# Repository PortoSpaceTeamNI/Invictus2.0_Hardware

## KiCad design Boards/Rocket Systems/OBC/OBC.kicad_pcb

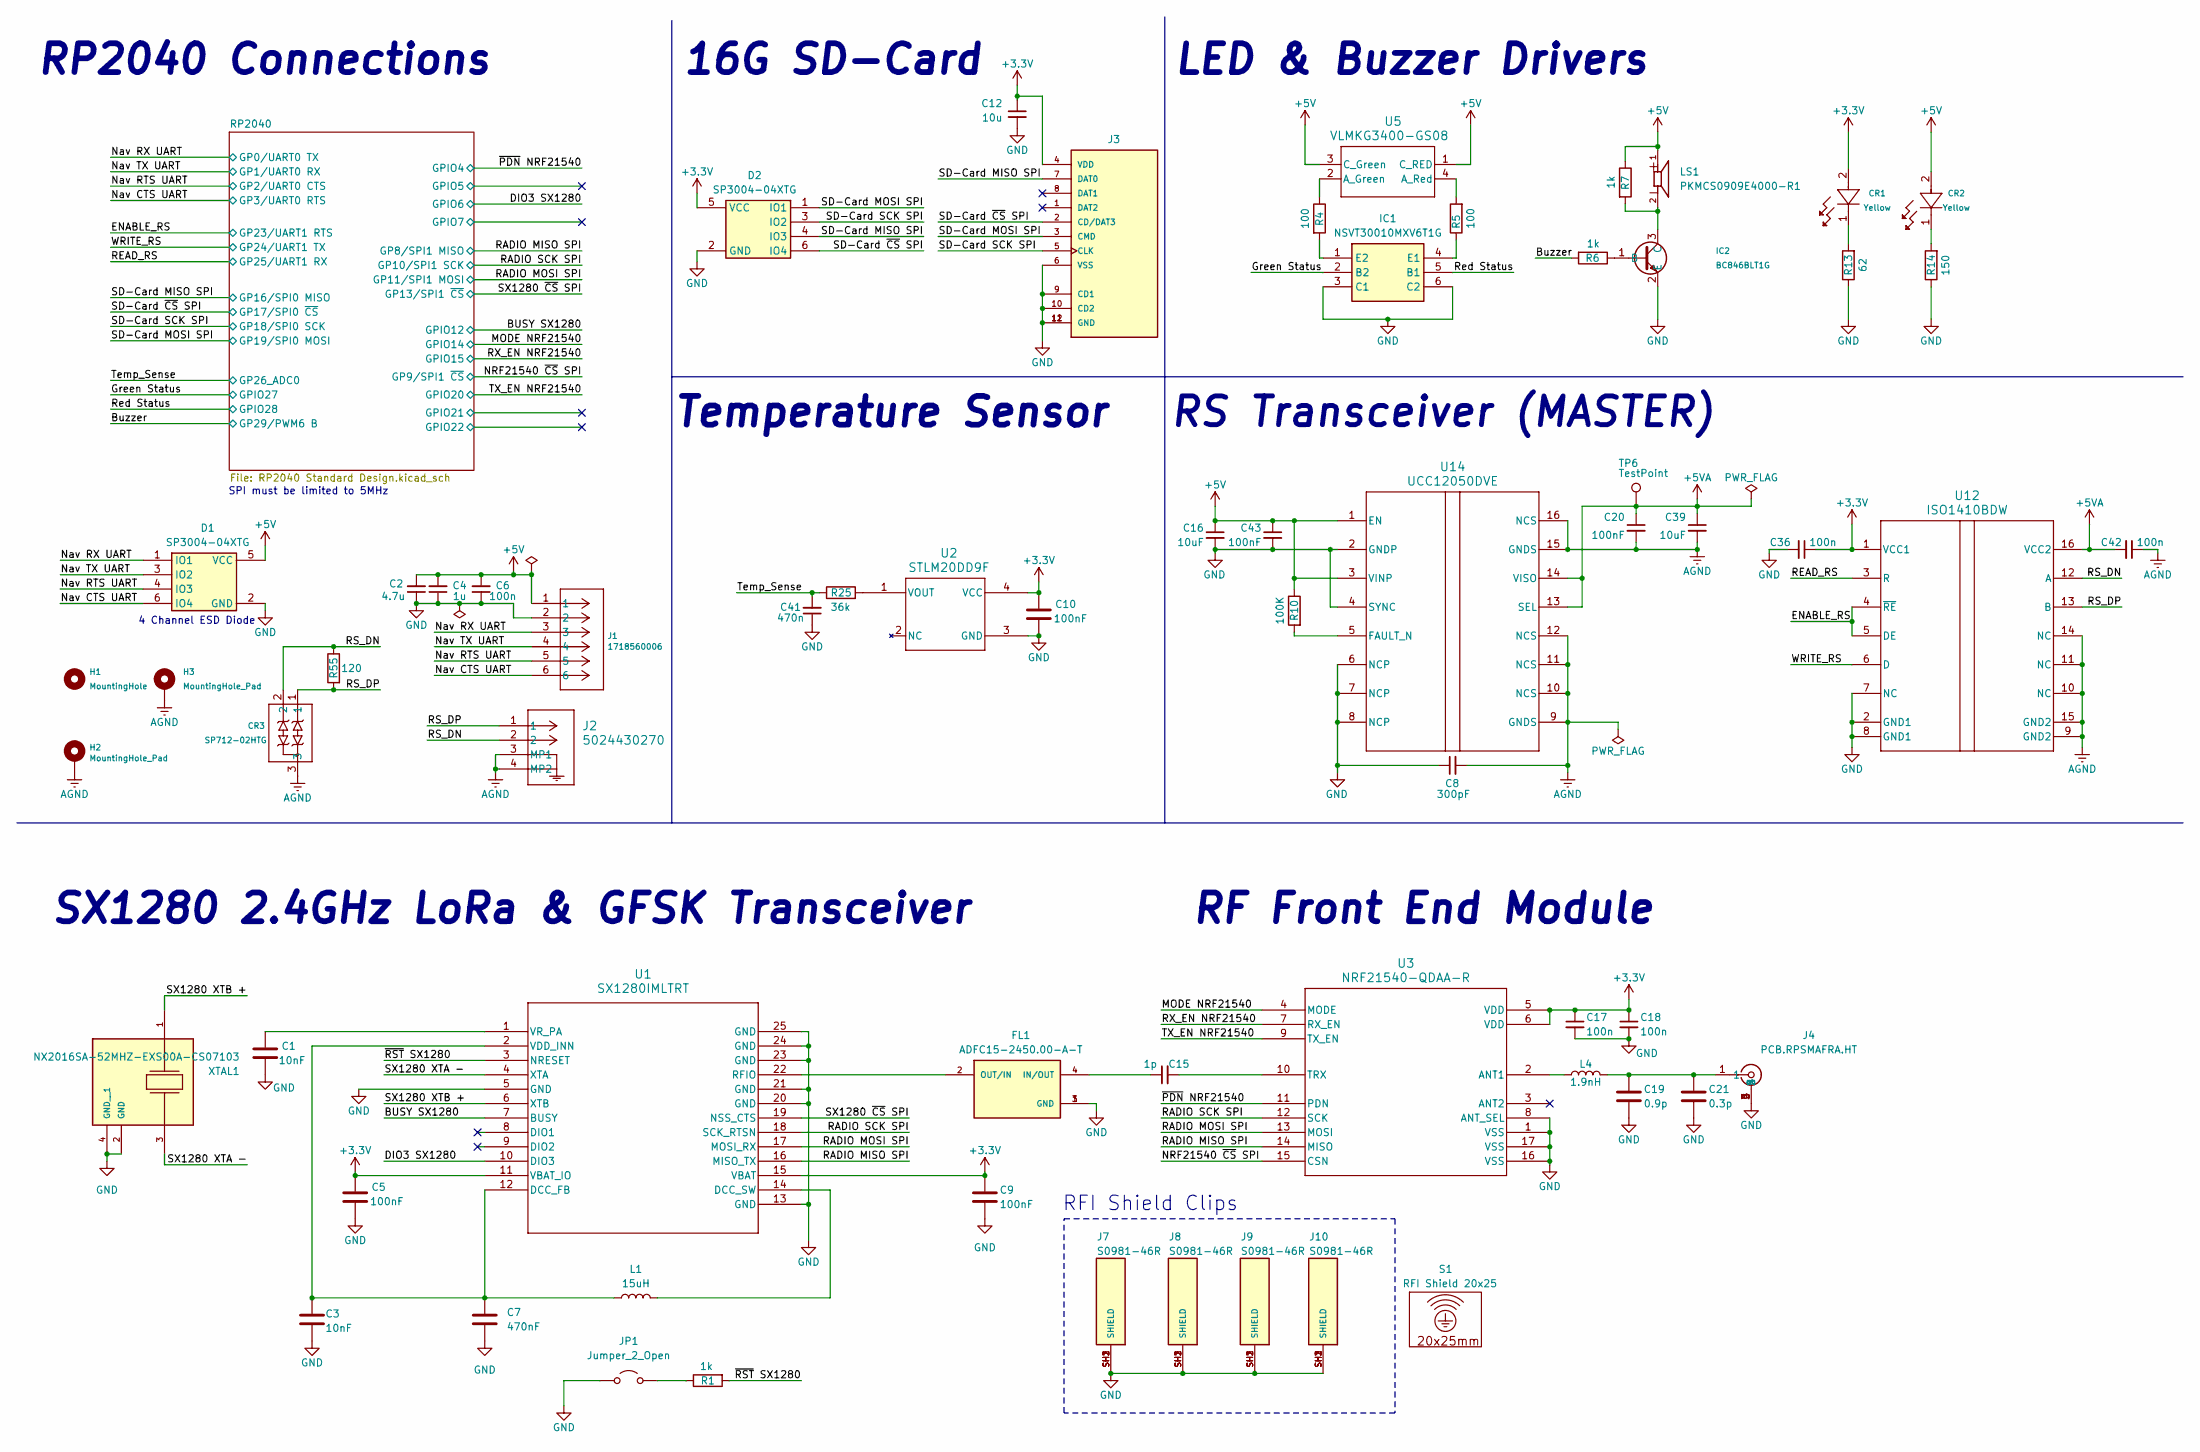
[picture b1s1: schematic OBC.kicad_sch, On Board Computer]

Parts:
C1, C3: 10nF; Capacitor_0402
C2: 4.7u; Capacitor_0603
C4: 1u; Capacitor_0402
C5, C9, C10, C20, C43: 100nF; Capacitor_0402
C6, C17, C18, C36, C42: 100n; Capacitor_0402
C7: 470nF; Capacitor_0402
C8: 300pF; C1808
C12: 10u; Capacitor_0805
C15: 1p; Capacitor_0402
C16, C39: 10uF; Capacitor_0805
C19: 0.9p; Capacitor_0402
C21: 0.3p; Capacitor_0402
C41: 470n; Capacitor_0402
CR1, CR2: VLMY1300-GS08; LEDC1608X100N
CR3: SP712-02HTG; SOT23-3_LTF
D1, D2: SP3004-04XTG; SOT563_LTF; Mouser Part Number 576-SP3004-04XTG
FL1: ADFC15-2450.00-A-T; FIL_ADFC15-2450.00-A-T; PARTREV 12.03.12
H1: MountingHole; MountingHole_3.2mm_M3_ISO7380
H2, H3: MountingHole_Pad; MountingHole_3.2mm_M3_ISO7380_Pad
IC1: NSVT30010MXV6T1G; SOTFL50P160X60-6N; Mouser Part Number 863-NSVT30010MXV6T1G
IC2: BC846BLT1G; SOT-23_ONS; Mouser Part Number 863-BC846BLT1G
J1: 1718560006; CONN06_1718560006_MOL
J2: 5024430270; CONN_502443-02xx_MOL
J3: MEM2061-01-188-00-A_REVA; GCT_MEM2061-01-188-00-A_REVA
J4: PCB.RPSMAFRA.HT; PCBRPSMAFRAHT; Mouser Part Number 960-PCB.RPSMAFRA.HT
J7, J8, J9, J10: S0981-46R; HARWIN_S0981-46R; PARTREV 3
JP1: Jumper_2_Open; SolderJumper-2_P1.3mm_Open_RoundedPad1.0x1.5mm
L1: 15uH; Inductor_0805
L4: 1.9nH; Inductor_0201
LS1: PKMCS0909E4000-R1; SPKR_PKMCS0909E4000-R1; PARTREV May 22, 2020
R1: 1k; RES_0402
R4, R5: 100; RES_0603
R6, R7: 1k; RES_0603
R10: 100K; RES_0402
R13: 62; RES_0603
R14: 150; RES_0603
R25: 36k; RES_0402
R55: 120; RES_0603
S1: RFI Shield 20x25; RFI Shield
TP6: TestPoint; TestPoint_Pad_2.0x2.0mm
U1: SX1280IMLTRT; QFN24_4X4_SEM
U2: STLM20DD9F; UDFN-4L_STM
U3: NRF21540-QDAA-R; QFN16_4X4_NOR
U5: VLMKG3400-GS08; SMT_00-GS08_VIS
U12: ISO1410BDW; DW0016B_N
U14: UCC12050DVE; DVE0016A
XTAL1: NX2016SA-52MHZ-EXS00A-CS07103; OSCCC200X160X50N; PARTREV N/A

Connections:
+3.3V: C5.1, C9.1, C10.1, C12.1, C17.1, C18.1, C36.1, CR1.2, D2.5 (VCC), J3.4 (VDD), U1.11 (VBAT_IO), U1.15 (VBAT), U2.4 (VCC), U3.5 (VDD), U3.6 (VDD), U12.1 (VCC1); also elsewhere on the board
+5V: C2.2, C4.2, C6.2, C16.1, C43.1, CR2.2, D1.5 (VCC), J1.1, LS1.1, R7.1, R10.1, U5.1 (C_RED), U5.3 (C_Green), U14.1 (EN), U14.3 (VINP); also elsewhere on the board
+5VA: C20.1, C39.1, C42.2, TP6.1, U12.16 (VCC2), U14.13 (SEL), U14.14 (VISO)
/BUSY SX1280: U1.7 (BUSY); also elsewhere on the board
/Buzzer: R6.2; also elsewhere on the board
/DIO3 SX1280: U1.10 (DIO3); also elsewhere on the board
/ENABLE_RS: U12.4 (~RE), U12.5 (DE); also elsewhere on the board
/Green Status: IC1.2 (B2); also elsewhere on the board
/MODE NRF21540: U3.4 (MODE); also elsewhere on the board
/NRF21540 ~CS SPI: U3.15 (CSN); also elsewhere on the board
/Nav CTS UART: D1.6 (IO4), J1.6; also elsewhere on the board
/Nav RTS UART: D1.4 (IO3), J1.5; also elsewhere on the board
/Nav RX UART: D1.1 (IO1), J1.3; also elsewhere on the board
/Nav TX UART: D1.3 (IO2), J1.4; also elsewhere on the board
/RADIO MISO SPI: U1.16 (MISO_TX), U3.14 (MISO); also elsewhere on the board
/RADIO MOSI SPI: U1.17 (MOSI_RX), U3.13 (MOSI); also elsewhere on the board
/RADIO SCK SPI: U1.18 (SCK_RTSN), U3.12 (SCK); also elsewhere on the board
/READ_RS: U12.3 (R); also elsewhere on the board
/RS_DN: CR3.2, J2.2, R55.1, U12.12 (A)
/RS_DP: CR3.1, J2.1, R55.2, U12.13 (B)
/RX_EN NRF21540: U3.7 (RX_EN); also elsewhere on the board
/Red Status: IC1.5 (B1); also elsewhere on the board
/SD-Card ~CS SPI: D2.6 (IO4), J3.2 (CD/DAT3); also elsewhere on the board
/SD-Card MISO SPI: D2.4 (IO3), J3.7 (DAT0); also elsewhere on the board
/SD-Card MOSI SPI: D2.1 (IO1), J3.3 (CMD); also elsewhere on the board
/SD-Card SCK SPI: D2.3 (IO2), J3.5 (CLK); also elsewhere on the board
/SX1280 XTA -: U1.4 (XTA), XTAL1.3
/SX1280 XTB +: U1.6 (XTB), XTAL1.1
/SX1280 ~CS SPI: U1.19 (NSS_CTS); also elsewhere on the board
/TX_EN NRF21540: U3.9 (TX_EN); also elsewhere on the board
/Temp_Sense: C41.2, R25.1; also elsewhere on the board
/WRITE_RS: U12.6 (D); also elsewhere on the board
/~PDN NRF21540: U3.11 (PDN); also elsewhere on the board
/~RST SX1280: R1.2, U1.3 (NRESET)
AGND: C8.2, C20.2, C39.2, C42.1, CR3.3, H2.1, H3.1, J2.3 (MP1), J2.4 (MP2), U12.9 (GND2), U12.10 (NC), U12.11 (NC), U12.14 (NC), U12.15 (GND2), U14.9 (GNDS), U14.10 (NCS), U14.11 (NCS), U14.12 (NCS), U14.15 (GNDS), U14.16 (NCS)
GND: C1.2, C2.1, C3.2, C4.1, C5.2, C6.1, C7.2, C8.1, C9.2, C10.2, C12.2, C16.2, C17.2, C18.2, C19.2, C21.2, C36.2, C41.1, C43.2, D1.2 (GND), D2.2 (GND), FL1.1 (GND), FL1.3 (GND), IC1.3 (C1), IC1.6 (C2), IC2.2 (E), J1.2, J3.6 (VSS), J3.9 (CD1), J3.10 (CD2), J3.11 (GND), J3.12 (GND), J4.2, J4.3, J4.4, J4.5, J7.SH1 (SHIELD), J7.SH2 (SHIELD), J7.SH3 (SHIELD), J8.SH1 (SHIELD), J8.SH2 (SHIELD), J8.SH3 (SHIELD), J9.SH1 (SHIELD), J9.SH2 (SHIELD), J9.SH3 (SHIELD), J10.SH1 (SHIELD), J10.SH2 (SHIELD), J10.SH3 (SHIELD), JP1.1 (A), R13.1, R14.1, U1.5 (GND), U1.13 (GND), U1.20 (GND), U1.21 (GND), U1.23 (GND), U1.24 (GND), U1.25 (GND), U2.3 (GND), U3.1 (VSS), U3.8 (ANT_SEL), U3.16 (VSS), U3.17 (VSS), U12.2 (GND1), U12.7 (NC), U12.8 (GND1), U14.2 (GNDP), U14.4 (SYNC), U14.6 (NCP), U14.7 (NCP), U14.8 (NCP), XTAL1.2 (GND), XTAL1.4 (GND__1); also elsewhere on the board
unnamed: C19.1, C21.1, J4.1, L4.2
unnamed: CR1.1, R13.2
unnamed: CR2.1, R14.2
unnamed: C15.1, FL1.4 (IN/OUT)
unnamed: FL1.2 (OUT/IN), U1.22 (RFIO)
unnamed: IC1.4 (E1), R5.1
unnamed: IC1.1 (E2), R4.2
unnamed: IC2.1 (B), R6.1
unnamed: IC2.3 (C), LS1.2, R7.2
unnamed: JP1.2 (B), R1.1
unnamed: C3.1, C7.1, L1.1, U1.2 (VDD_INN), U1.12 (DCC_FB)
unnamed: L1.2, U1.14 (DCC_SW)
unnamed: C1.1, U1.1 (VR_PA)
unnamed: R25.2, U2.1 (VOUT)
unnamed: L4.1, U3.2 (ANT1)
unnamed: C15.2, U3.10 (TRX)
unnamed: R4.1, U5.2 (A_Green)
unnamed: R5.2, U5.4 (A_Red)
unnamed: R10.2, U14.5 (FAULT_N)

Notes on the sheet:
RF Front End Module
Temperature Sensor
SX1280 2.4GHz LoRa & GFSK Transceiver
RP2040 Connections
SPI must be limited to 5MHz
16G SD-Card
RS Transceiver (MASTER)
LED & Buzzer Drivers
RFI Shield Clips
4 Channel ESD Diode

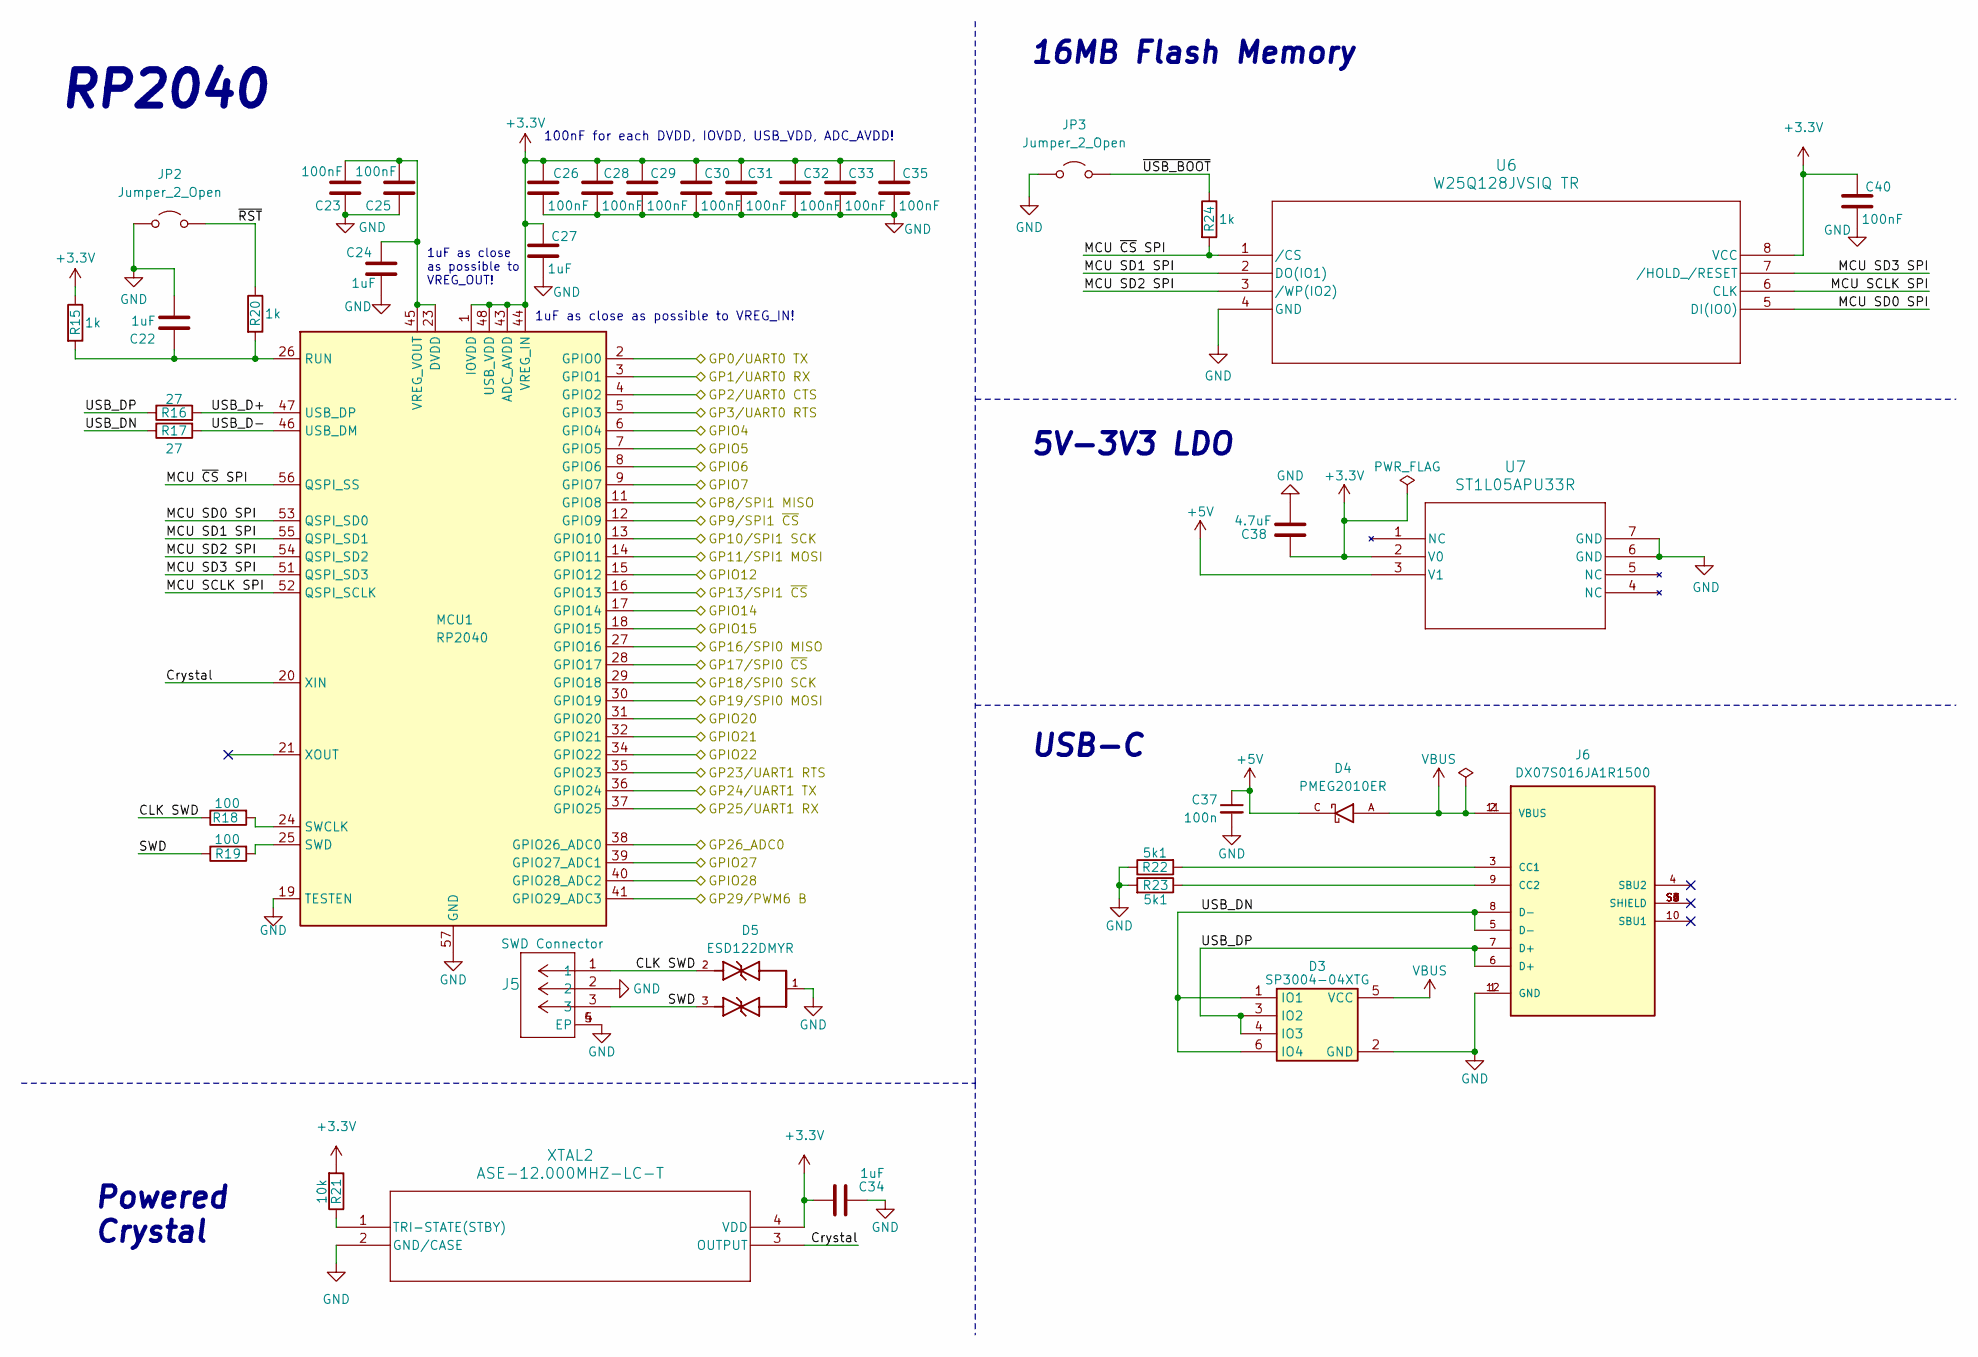
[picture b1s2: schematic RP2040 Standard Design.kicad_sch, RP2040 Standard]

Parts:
C22, C24, C27, C34: 1uF; Capacitor_0402
C23, C25, C26, C28, C29, C30, C31, C32, C33, C35, C40: 100nF; Capacitor_0402
C37: 100n; Capacitor_0402
C38: 4.7uF; Capacitor_0603
D3: SP3004-04XTG; SOT563_LTF; Mouser Part Number 576-SP3004-04XTG
D4: PMEG2010ER; SODFL3517X110N; PARTREV 01
D5: ESD122DMYR; DIO_ESD122DMYR; PARTREV A
J5: BM03B-SRSS-TBLFSN; CONN_BM03B-SRSS-TBLFSN_JST
J6: DX07S016JA1R1500; JAE_DX07S016JA1R1500; PARTREV 1
JP2, JP3: Jumper_2_Open; SolderJumper-2_P1.3mm_Open_RoundedPad1.0x1.5mm
MCU1: RP2040; QFN56_7X7_RPI
R15, R20, R24: 1k; RES_0402
R16, R17: 27; RES_0402
R18, R19: 100; RES_0402
R21: 10k; RES_0402
R22, R23: 5k1; RES_0402
U6: W25Q128JVSIQ TR; SOIC_208MIL_WIN
U7: ST1L05APU33R; DFN_5APU33R_STM
XTAL2: ASE-12.000MHZ-LC-T; ASE24576MHZLCT

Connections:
+3.3V: C26.1, C27.1, C28.1, C29.1, C30.1, C31.1, C32.1, C33.1, C34.1, C35.1, C38.2, C40.1, MCU1.1 (IOVDD), MCU1.10 (IOVDD), MCU1.22 (IOVDD), MCU1.33 (IOVDD), MCU1.42 (IOVDD), MCU1.43 (ADC_AVDD), MCU1.44 (VREG_IN), MCU1.48 (USB_VDD), MCU1.49 (IOVDD), R15.1, R21.2, U6.8 (VCC), U7.2 (V0), XTAL2.4 (VDD); also elsewhere on the board
+5V: C37.1, D4.C, U7.3 (V1); also elsewhere on the board
/BUSY SX1280: MCU1.15 (GPIO12); also elsewhere on the board
/Buzzer: MCU1.41 (GPIO29_ADC3); also elsewhere on the board
/DIO3 SX1280: MCU1.8 (GPIO6); also elsewhere on the board
/ENABLE_RS: MCU1.35 (GPIO23); also elsewhere on the board
/Green Status: MCU1.39 (GPIO27_ADC1); also elsewhere on the board
/MODE NRF21540: MCU1.17 (GPIO14); also elsewhere on the board
/NRF21540 ~CS SPI: MCU1.12 (GPIO9); also elsewhere on the board
/Nav CTS UART: MCU1.5 (GPIO3); also elsewhere on the board
/Nav RTS UART: MCU1.4 (GPIO2); also elsewhere on the board
/Nav RX UART: MCU1.2 (GPIO0); also elsewhere on the board
/Nav TX UART: MCU1.3 (GPIO1); also elsewhere on the board
/RADIO MISO SPI: MCU1.11 (GPIO8); also elsewhere on the board
/RADIO MOSI SPI: MCU1.14 (GPIO11); also elsewhere on the board
/RADIO SCK SPI: MCU1.13 (GPIO10); also elsewhere on the board
/READ_RS: MCU1.37 (GPIO25); also elsewhere on the board
/RP2040/CLK SWD: D5.2, J5.1, R18.1
/RP2040/Crystal: MCU1.20 (XIN), XTAL2.3 (OUTPUT)
/RP2040/GPIO5: MCU1.7 (GPIO5)
/RP2040/GPIO7: MCU1.9 (GPIO7)
/RP2040/GPIO21: MCU1.32 (GPIO21)
/RP2040/GPIO22: MCU1.34 (GPIO22)
/RP2040/MCU SCLK SPI: MCU1.52 (QSPI_SCLK), U6.6 (CLK)
/RP2040/MCU SD0 SPI: MCU1.53 (QSPI_SD0), U6.5 (DI(IO0))
/RP2040/MCU SD1 SPI: MCU1.55 (QSPI_SD1), U6.2 (DO(IO1))
/RP2040/MCU SD2 SPI: MCU1.54 (QSPI_SD2), U6.3 (/WP(IO2))
/RP2040/MCU SD3 SPI: MCU1.51 (QSPI_SD3), U6.7 (/HOLD_/RESET)
/RP2040/MCU ~CS SPI: MCU1.56 (QSPI_SS), R24.2, U6.1 (/CS)
/RP2040/SWD: D5.3, J5.3, R19.1
/RP2040/USB_D+: MCU1.47 (USB_DP), R16.2
/RP2040/USB_D-: MCU1.46 (USB_DM), R17.2
/RP2040/USB_DN: D3.1 (IO1), D3.6 (IO4), J6.5 (D-), J6.8 (D-), R17.1
/RP2040/USB_DP: D3.3 (IO2), D3.4 (IO3), J6.6 (D+), J6.7 (D+), R16.1
/RP2040/~RST: JP2.2 (B), R20.1
/RP2040/~USB_BOOT: JP3.2 (B), R24.1
/RX_EN NRF21540: MCU1.18 (GPIO15); also elsewhere on the board
/Red Status: MCU1.40 (GPIO28_ADC2); also elsewhere on the board
/SD-Card ~CS SPI: MCU1.28 (GPIO17); also elsewhere on the board
/SD-Card MISO SPI: MCU1.27 (GPIO16); also elsewhere on the board
/SD-Card MOSI SPI: MCU1.30 (GPIO19); also elsewhere on the board
/SD-Card SCK SPI: MCU1.29 (GPIO18); also elsewhere on the board
/SX1280 ~CS SPI: MCU1.16 (GPIO13); also elsewhere on the board
/TX_EN NRF21540: MCU1.31 (GPIO20); also elsewhere on the board
/Temp_Sense: MCU1.38 (GPIO26_ADC0); also elsewhere on the board
/WRITE_RS: MCU1.36 (GPIO24); also elsewhere on the board
/~PDN NRF21540: MCU1.6 (GPIO4); also elsewhere on the board
GND: C22.2, C23.1, C24.2, C25.1, C26.2, C27.2, C28.2, C29.2, C30.2, C31.2, C32.2, C33.2, C34.2, C35.2, C37.2, C38.1, C40.2, D3.2 (GND), D5.1, J5.2, J5.4 (EP), J5.5 (EP), J6.1 (GND), J6.12 (GND), JP2.1 (A), JP3.1 (A), MCU1.19 (TESTEN), MCU1.57 (GND), R22.1, R23.2, U6.4 (GND), U7.6 (GND), U7.7 (GND), XTAL2.2 (GND/CASE); also elsewhere on the board
unnamed: J6.3 (CC1), R22.2
unnamed: J6.9 (CC2), R23.1
unnamed: C22.1, MCU1.26 (RUN), R15.2, R20.2
unnamed: MCU1.24 (SWCLK), R18.2
unnamed: MCU1.25 (SWD), R19.2
unnamed: C23.2, C24.1, C25.2, MCU1.23 (DVDD), MCU1.45 (VREG_VOUT), MCU1.50 (DVDD)
unnamed: R21.1, XTAL2.1 (TRI-STATE(STBY))
VBUS: D3.5 (VCC), D4.A, J6.2 (VBUS), J6.11 (VBUS)

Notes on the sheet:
100nF for each DVDD, IOVDD, USB_VDD, ADC_AVDD!
16MB Flash Memory
5V-3V3 LDO
USB-C
1uF as close as possible to VREG_IN!
1uF as close as possible to VREG_OUT!
Powered Crystal
RP2040

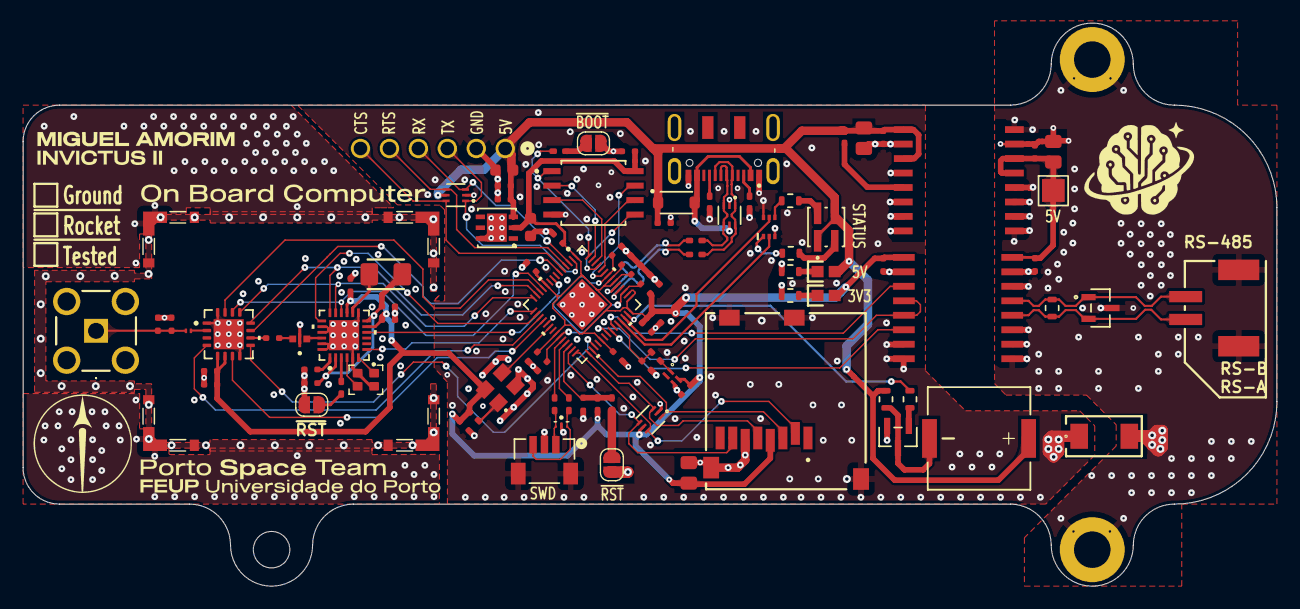
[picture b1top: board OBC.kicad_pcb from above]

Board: 4 copper layers, 110.0 x 49.4 mm, 103 parts (1 on the bottom side), 78 nets.

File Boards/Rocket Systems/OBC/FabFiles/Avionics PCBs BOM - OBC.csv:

On Board Computer,,,,,,,
Qty,Value,Parts,Device,Package,Description,Mouser Electronics,Digikey
2,VLMY1300-GS08,"CR1, CR2",VLMY1300-GS08,LEDC1608X100N,Yellow LED,78-VLMY1300-GS08,
1,SP712-02HTG,CR3,SP712-02HTG,SOT23-3_LTF,ESD/TVS protection Diode,576-SP712-02HTG ,
3,SP3004-04XTG,"D1, D2, D3",SP3004-04XTG,SOT563_LTF,ESD/TVS protection Diode,576-SP3004-04XTG ,
1,PMEG2010ER,D4,PMEG2010ER,SODFL3517X110N,Nexperia Schottky Diode ,771-PMEG2010ER115,
1,ESD122DMYR,D5,ESD122DMYR,DIO_ESD122DMYR,ESD/TVS protection Diode,595-ESD122DMYR,
1,ADFC15-2450.00-A-T,FL1,ADFC15-2450.00-A-T,FIL_ADFC15-2450.00-A-T,2.45GHz Bandpass Filter,815-ADFC15-2450-AT ,
1,NSVT30010MXV6T1G,IC1,NSVT30010MXV6T1G,SOT-563_1P3X1P7_ONS,Dual BJT PNP,863-NSVT30010MXV6T1G,
1,BC846BLT1G,IC2,BC846BLT1G,SOT96P237X111-3N,BJT NPN Transistor,863-BC846BLT1G,
1,RP2040,MCU1,RP2040,QFN56_7X7_RPI,RP2040,358-SC091413 ,
1,PKMCS0909E4000-R1,LS1,PKMCS0909E4000-R1,SPKR_PKMCS0909E4000-R1,Piezoelectric Buzzer,81-PKLCS1212E20A0-R1,
1,SX1280IMLTRT,U1,SX1280IMLTRT,QFN24_4X4_SEM,2.4GHz LoRa radio transceiver,947-SX1280IMLTRT ,
1,STLM20DD9F,U2,STLM20DD9F,UDFN-4L_STM,Analog Temperature Sensor,511-STLM20DD9F ,
1,NRF21540-QDAA-R,U3,NRF21540-QDAA-R,QFN16_4X4_NOR,RF Range Extender FEM,949-NRF21540-QDAA-R ,
1,VLMKG3400-GS08,U5,VLMKG3400-GS08,SMT_00-GS08_VIS,BiColor Red/Green LED PLCC4,78-VLMKG3400-GS08 ,
1,W25Q128JVSIQ TR,U6,W25Q128JVSIQ TR,SOIC_208MIL_WIN,Windbond NOR Flash 16MB,454-W25Q128JVSIQTR ,
1,ST1L05APU33R,U7,ST1L05APU33R,DFN_5APU33R_STM,ST Voltage Regulator LDO 5V to 3.3V, 511-ST1L05APU33R,
1,ISO1410BDW,U12,ISO1410BDW,DW0016B_N,Galvanically Isolated RS-485 Half-Duplex Transceiver ,595-ISO1410BDW ,
1,UCC12050DVE,U14,UCC12050DVE,DVE0016A,Galvanically Isolated 5V DC-DC Converter,595-UCC12050DVE ,
1,CS07103-52M,XTAL1,CS07103-52M,OSCCC200X160X50N,Crystal 52MHz,,644-CS07103-52MDKR-ND
1,ASE-12.000MHZ-LC-T,XTAL2,ASE-12.000MHZ-LC-T,ASE24576MHZLCT,Clock Oscilator,815-ASE12.000MHZLCT ,
22,100nF,"C5, C6, C9, C10, C17, C18, C20, C23, C25, C26, C28, C29, C30, C31, C32, C33, C35, C36, C37, C40, C42, C43",GPC0402104-16,C0402,CAPACITOR,,
5,1uF,"C4, C22, C24, C27, C34",GPC0402105-16,C0402,CAPACITOR,,
2,10nF,"C1, C3",GPC0402103-16,C0402,CAPACITOR,,
2,470nF,"C7, C41",GPC0402474-25,C0402,CAPACITOR,,
1,1pF,C15,GPC04021R0,C0402,CAPACITOR,,
1,0.9pF,C19,GRM1555C1ER90BA01D,C0402,CAPACITOR, 81-GRM1555C1ER90BA1D,
1,0.3pF,C21,GRM1555C2AR30BA01D,C0402,CAPACITOR,81-GRM1555C2AR30BA1D ,
2,4.7uF,"C2, C38",GPC0603475-10,C0603,CAPACITOR,,
3,10uF,"C12, C16, C39",GPC0805106-16,C0805,CAPACITOR,,
1,300pF,C8,C1808C331JZGACTU ,C1808,CAPACITOR,80-C1808C331JZG ,
4,1k,"R1, R15, R20, R24",GPR04021K,R0402,RESISTOR,,
2,27,"R16, R17",GPR040227R,R0402,RESISTOR,,
2,100,"R18, R19",GPR0402100R,R0402,RESISTOR,,
2,5k1,"R22, R23",GPR04025K1,R0402,RESISTOR,,
1,100K,R10,GPR0402100K,R0402,RESISTOR,,
1,10k,R21,GPR040210K,R0402,RESISTOR,,
1,36k,R25,GPR040236K,R0402,RESISTOR,,
2,100,"R4, R5",GPR0603100R,R0603,RESISTOR,,
2,1k,"R6, R7",GPR06031K,R0603,RESISTOR,,
1,62,R13,GPR060362R,R0603,RESISTOR,,
1,150,R14,GPR0603150R,R0603,RESISTOR,,
1,120,R55,GPR0603120R,R0603,RESISTOR,,
1,15uH,L1,B82422H1153K000 ,L0805,INDUCTOR,871-B82422H1153K ,
1,1.9nH,L4,LQW03AW1N9C00D ,L0201,INDUCTOR,81-LQW03AW1N9C00D,
1,1718560006,J1,1718560006,CONN06_1718560006_MOL,Vertical PCB Header 6 Circuits with Friction Lock,538-171856-0006,
1,215932-0270,J2,215932-0270,2159320270,Pitch Mini-Lock PCB Header Single Row Right-Angle SMT 2 Circuits ,538-215932-0270 ,
1,MEM2061-01-188-00-A_REVA,J3,MEM2061-01-188-00-A_REVA,GCT_MEM2061-01-188-00-A_REVA,MicroSD Card Slot connector,640-MEM20610118800A ,
1,PCB.RPSMAFRA.HT,J4,PCB.RPSMAFRA.HT,PCBRPSMAFRAHT,RP-SMA Female PCB connector,960-PCB.RPSMAFRA.HT,
1,BM03B-SRSS-TBLFSN,J5,BM03B-SRSS-TBLFSN,CONN_BM03B-SRSS-TBLFSN_JST,SWD Connector,306-BM03BSRSSTBLFSNP ,
1,DX07S016JA1R1500,J6,DX07S016JA1R1500,JAE_DX07S016JA1R1500,USB-C receptacle,656-DX07S016JA1R1500 ,
4,S0981-46R,"J7, J8, J9, J10",S0981-46R,HARWIN_S0981-46R,EMI Shield Clips,855-S0991-46R ,
1,S01-30300500,S1,S01-30300500 ,RFI Shield 30x30,RFI/EMI Shield Gasket,855-S01-30300500 ,

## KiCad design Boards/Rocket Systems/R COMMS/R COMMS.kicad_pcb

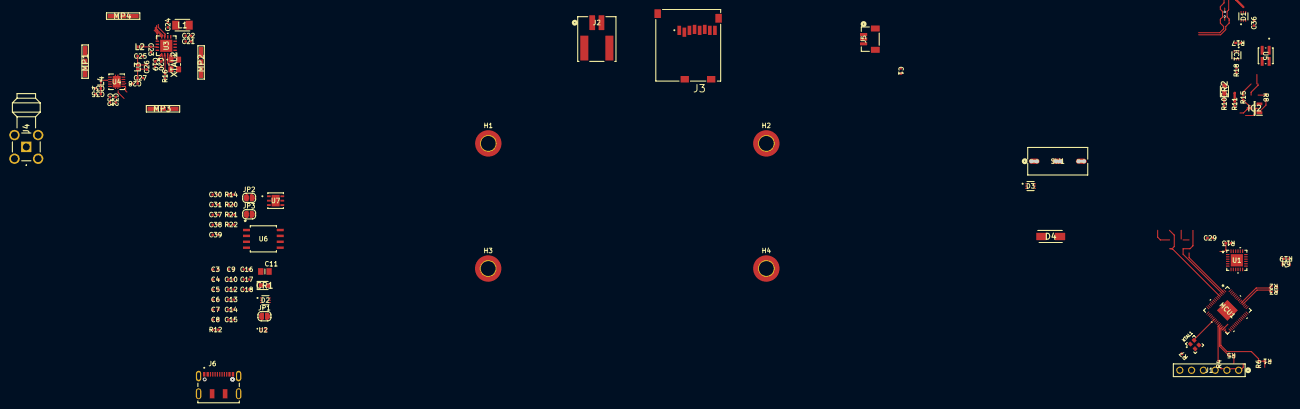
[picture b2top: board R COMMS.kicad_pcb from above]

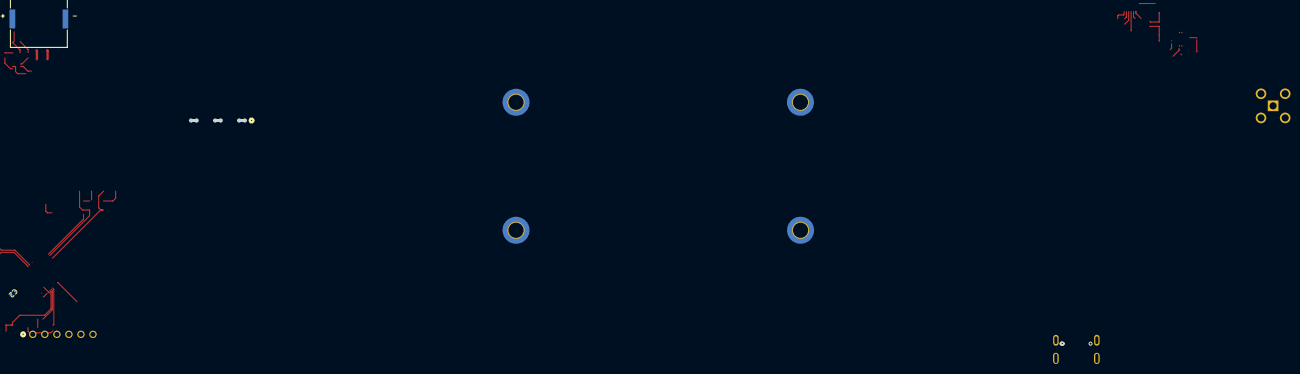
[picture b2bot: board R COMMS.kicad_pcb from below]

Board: 4 copper layers, 102 parts (2 on the bottom side), 78 nets.

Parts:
C1, C2: 10nF; Capacitor_0402
C3, C5: 4.7u; Capacitor_0402
C4, C8, C9, C22, C24, C25, C27, C28, C29, C30, C31, C32, C34, C39: 100nF; Capacitor_0402
C6: 470nF; Capacitor_0402
C7: 0.8pF; Capacitor_0402
C10, C13: 1.2pF; Capacitor_0402
C11: 10u; Capacitor_0805
C12: 0.5pF; Capacitor_0402
C14: 1p; Capacitor_0402
C15, C16, C17, C19, C36: 100n; Capacitor_0402
C18: 0.9p; Capacitor_0402
C20: 0.3p; Capacitor_0402
C21, C23, C26, C33, C38: 1uF; Capacitor_0402
C35, C37: 4.7uF; Capacitor_0402
CR1, CR2: VLMY1300-GS08; LEDC1608X100N
D1, D2, D3: SP3004-04XTG; SOT563_LTF
D4: RSX301L-30DDTE25; DIOM5026X220N
H1, H2, H3, H4: MountingHole; MountingHole_3.2mm_M3_ISO7380_Pad_TopBottom
IC1: NSVT30010MXV6T1G; SOT-563_1P3X1P7_ONS
IC2: BC846BLT1G; SOT96P237X111-3N
J1: 22285061; CONN_SD-42375-001_M320_06_MOL
J2: 5023520200; CONN02_502352_MOL
J3: MEM2061-01-188-00-A_REVA; GCT_MEM2061-01-188-00-A_REVA
J4: SMARA_CONNECTOR; SMARACONNECTOR
J5: BM03B-SRSS-TBLFSN; CONN_BM03B-SRSS-TBLFSN_JST
J6: DX07S016JA1R1500; JAE_DX07S016JA1R1500
JP1, JP2, JP3: Jumper_2_Open; SolderJumper-2_P1.3mm_Open_RoundedPad1.0x1.5mm
L1: 15uH; Inductor_0805
L2: 3nH; Inductor_0402
L3: 2.5nH; Inductor_0402
L4: 1.9nH; Inductor_0201
LS1: PKLCS1212E20A0-R1
MCU1: RP2040; QFN56_7X7_RPI
MP1, MP2, MP3, MP4: S0991-46R; S099146R
R1, R6, R7, R13, R18, R22: 1k; RES_0402
R2, R3, R19: 10k; RES_0402
R4, R5, R16, R17: 100; RES_0402
R8, R10: 523; RES_0402
R9: 120; RES_0603
R11: 65; RES_0402
R12: 150; RES_0402
R14, R15: 27; RES_0402
R20, R21: 5k1; RES_0402
SW1: D2F-01-D; D2F-01-D_OMR
U1: SX1280IMLTRT; QFN24_4X4_SEM
U2: STLM20DD9F; UDFN-4L_STM
U3: NRF21540-QDAA-R; QFN16_4X4_NOR
U4: THVD2410VDRCR; VSON10_DRC_TEX
U5: VLMKG3400-GS08; SMT_00-GS08_VIS
U6: W25Q128JVSIQ TR; SOIC_208MIL_WIN
U7: ST1L05APU33R; DFN_5APU33R_STM
XTAL1: NX2016SA-52MHZ-EXS00A-CS07103; OSCCC200X160X50N
XTAL2: ASE-12.000MHZ-LC-T; ASE24576MHZLCT

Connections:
+3.3V: C4.1, C8.1, C9.1, C11.1, C15.2, C16.1, C17.1, C25.1, C26.1, C27.1, C28.1, C29.1, C30.1, C31.1, C32.1, C33.1, C34.1, C37.2, C39.1, CR1.2, D2.5 (VCC), J3.4 (VDD), MCU1.1 (IOVDD), MCU1.10 (IOVDD), MCU1.22 (IOVDD), MCU1.33 (IOVDD), MCU1.42 (IOVDD), MCU1.43 (ADC_AVDD), MCU1.44 (VREG_IN), MCU1.48 (USB_VDD), MCU1.49 (IOVDD), R2.1, R13.1, R19.2, U1.11 (VBAT_IO), U1.15 (VBAT), U2.4 (VCC), U3.5 (VDD), U3.6 (VDD), U4.1 (VIO), U6.8 (VCC), U7.2 (V0), XTAL2.4 (VDD)
+5V: C3.2, C5.2, C19.1, C35.2, C36.1, C38.2, CR2.2, D1.5 (VCC), D4.1 (K), J1.1, LS1.P, R7.1, R8.1, SW1.2, U4.10 (VCC), U5.1 (C_RED), U5.3 (C_Green), U7.3 (V1)
/BUSY SX1280: MCU1.31 (GPIO20), U1.7 (BUSY)
/Buzzer: MCU1.37 (GPIO25), R6.2
/DIO1 SX1280: MCU1.32 (GPIO21), U1.8 (DIO1)
/DIO2 SX1280: MCU1.34 (GPIO22), U1.9 (DIO2)
/DIO3 SX1280: MCU1.35 (GPIO23), U1.10 (DIO3)
/ENABLE_RS: MCU1.8 (GPIO6), R3.1, U4.3 (DE), U4.4 (~RE)
/Green Status: IC1.2 (B2), MCU1.39 (GPIO27_ADC1)
/MODE NRF21540: MCU1.15 (GPIO12), U3.4 (MODE)
/NRF21540 ~CS SPI: MCU1.12 (GPIO9), U3.15 (CSN)
/Nav CTS UART: D1.6 (IO4), J1.6, MCU1.5 (GPIO3)
/Nav RTS UART: D1.3 (IO2), J1.5, MCU1.4 (GPIO2)
/Nav RX UART: D1.1 (IO1), J1.3, MCU1.2 (GPIO0)
/Nav TX UART: D1.4 (IO3), J1.4, MCU1.3 (GPIO1)
/RADIO MISO SPI: MCU1.14 (GPIO11), U1.16 (MISO_TX), U3.14 (MISO)
/RADIO MOSI SPI: MCU1.13 (GPIO10), U1.17 (MOSI_RX), U3.13 (MOSI)
/RADIO SCK SPI: MCU1.11 (GPIO8), U1.18 (SCK_RTSN), U3.12 (SCK)
/READ_RS: MCU1.7 (GPIO5), R2.2, U4.2 (R)
/RP2040/CLK SWD: J5.1, R16.1
/RP2040/Crystal: MCU1.20 (XIN), XTAL2.3 (OUTPUT)
/RP2040/MCU SCLK SPI: MCU1.52 (QSPI_SCLK), U6.6 (CLK)
/RP2040/MCU SD0 SPI: MCU1.53 (QSPI_SD0), U6.5 (DI(IO0))
/RP2040/MCU SD1 SPI: MCU1.55 (QSPI_SD1), U6.2 (DO(IO1))
/RP2040/MCU SD2 SPI: MCU1.54 (QSPI_SD2), U6.3 (/WP(IO2))
/RP2040/MCU SD3 SPI: MCU1.51 (QSPI_SD3), U6.7 (/HOLD_/RESET)
/RP2040/MCU ~CS SPI: MCU1.56 (QSPI_SS), R22.2, U6.1 (/CS)
/RP2040/SWD: J5.3, R17.1
/RP2040/USB_D+: MCU1.47 (USB_DP), R14.2
/RP2040/USB_D-: MCU1.46 (USB_DM), R15.2
/RP2040/USB_DN: D3.3 (IO2), D3.6 (IO4), J6.5 (D-), J6.8 (D-), R15.1
/RP2040/USB_DP: D3.1 (IO1), D3.4 (IO3), J6.6 (D+), J6.7 (D+), R14.1
/RP2040/~RST: JP2.2 (B), R18.1
/RP2040/~USB_BOOT: JP3.2 (B), R22.1
/RS_DN: J2.1, R8.2, R9.1, U4.9 (B)
/RS_DP: J2.2, R9.2, R10.1, U4.8 (A)
/RX_EN NRF21540: MCU1.17 (GPIO14), U3.7 (RX_EN)
/Red Status: IC1.5 (B1), MCU1.40 (GPIO28_ADC2)
/SD-Card ~CS SPI: D2.4 (IO3), J3.2 (CD/DAT3), MCU1.28 (GPIO17)
/SD-Card MISO SPI: D2.1 (IO1), J3.7 (DAT0), MCU1.27 (GPIO16)
/SD-Card MOSI SPI: D2.3 (IO2), J3.3 (CMD), MCU1.30 (GPIO19)
/SD-Card SCK SPI: D2.6 (IO4), J3.5 (CLK), MCU1.29 (GPIO18)
/SX1280 XTA -: U1.4 (XTA), XTAL1.3
/SX1280 XTB +: U1.6 (XTB), XTAL1.1
/SX1280 ~CS SPI: MCU1.16 (GPIO13), U1.19 (NSS_CTS)
/TX_EN NRF21540: MCU1.18 (GPIO15), U3.9 (TX_EN)
/Temp_Sense: MCU1.38 (GPIO26_ADC0), U2.1 (VOUT)
/WRITE_RS: MCU1.6 (GPIO4), U4.5 (D)
/~PDN NRF21540: MCU1.9 (GPIO7), U3.11 (PDN)
/~RST SX1280: MCU1.36 (GPIO24), R1.2, U1.3 (NRESET)
GND: C1.2, C2.2, C3.1, C4.2, C5.1, C6.2, C7.2, C8.2, C9.2, C10.2, C11.2, C13.2, C15.1, C16.2, C17.2, C18.2, C19.2, C20.2, C21.2, C22.1, C23.2, C24.1, C25.2, C26.2, C27.2, C28.2, C29.2, C30.2, C31.2, C32.2, C33.2, C34.2, C35.1, C36.2, C37.1, C38.1, C39.2, D1.2 (GND), D2.2 (GND), D3.2 (GND), IC1.3 (C1), IC1.6 (C2), IC2.2 (E), J1.2, J3.6 (VSS), J3.9 (CD1), J3.10 (CD2), J3.11 (GND), J3.12 (GND), J4.2, J4.3, J4.4, J4.5, J5.2, J6.1 (GND), J6.12 (GND), JP1.1 (A), JP2.1 (A), JP3.1 (A), MCU1.19 (TESTEN), MCU1.57 (GND), MP1.1, MP1.2, MP1.3, MP2.1, MP2.2, MP2.3, MP3.1, MP3.2, MP3.3, MP4.1, MP4.2, MP4.3, R3.2, R10.2, R11.1, R12.1, R20.1, R21.2, SW1.1, U1.5 (GND), U1.13 (GND), U1.20 (GND), U1.21 (GND), U1.23 (GND), U1.24 (GND), U1.25 (GND), U2.3 (GND), U3.1 (VSS), U3.8 (ANT_SEL), U3.16 (VSS), U3.17 (VSS), U4.6 (GND), U4.11 (EPAD), U6.4 (GND), U7.6 (GND), U7.7 (GND), XTAL1.2 (GND), XTAL1.4 (GND__1), XTAL2.2 (GND/CASE)
unnamed: C10.1, C12.2, L2.2, L3.1
unnamed: C12.1, C13.1, C14.1, L3.2
unnamed: C18.1, C20.1, J4.1, L4.2
unnamed: CR1.1, R11.2
unnamed: CR2.1, R12.2
unnamed: IC1.4 (E1), R5.1
unnamed: IC1.1 (E2), R4.2
unnamed: IC2.1 (B), R6.1
unnamed: IC2.3 (C), LS1.N, R7.2
unnamed: J6.3 (CC1), R20.2
unnamed: J6.9 (CC2), R21.1
unnamed: JP1.2 (B), R1.1
unnamed: C21.1, MCU1.26 (RUN), R13.2, R18.2
unnamed: MCU1.24 (SWCLK), R16.2
unnamed: MCU1.25 (SWD), R17.2
unnamed: C22.2, C23.1, C24.2, MCU1.23 (DVDD), MCU1.45 (VREG_VOUT), MCU1.50 (DVDD)
unnamed: C2.1, C6.1, L1.1, U1.2 (VDD_INN), U1.12 (DCC_FB)
unnamed: L1.2, U1.14 (DCC_SW)
unnamed: C7.1, L2.1, U1.22 (RFIO)
unnamed: C1.1, U1.1 (VR_PA)
unnamed: L4.1, U3.2 (ANT1)
unnamed: C14.2, U3.10 (TRX)
unnamed: SW1.3, U4.7 (SLR)
unnamed: R4.1, U5.2 (A_Green)
unnamed: R5.2, U5.4 (A_Red)
unnamed: R19.1, XTAL2.1 (TRI-STATE(STBY))
VBUS: D3.5 (VCC), D4.2 (A), J6.2 (VBUS), J6.11 (VBUS)
